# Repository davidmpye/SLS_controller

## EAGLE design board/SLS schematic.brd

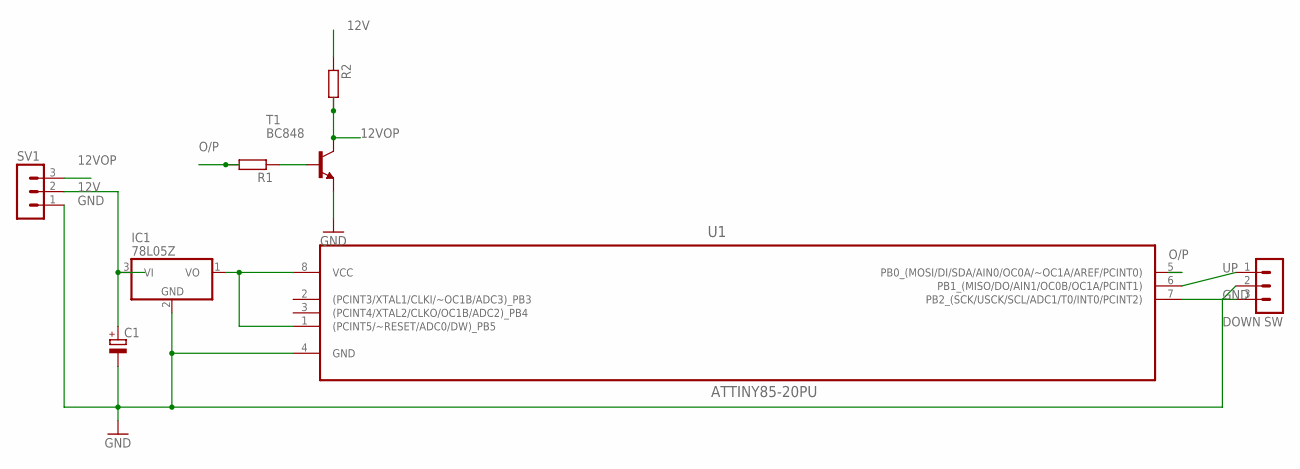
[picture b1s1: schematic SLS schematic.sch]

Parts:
C1: CPOL-EUCT3216; CT3216
IC1: 78L05Z; TO92
R1, R2: R-EU_R0805; R0805
SV1: MA03-1
SW: MA03-1
T1: BC848; SOT23
U1: ATTINY85-20PU; DIP254P762X533-8

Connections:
12V: C1.+, IC1.3 (VI), R2.1, SV1.2
12VOP: R2.2, SV1.3, T1.3 (C)
DOWN: SW.3, U1.7 (PB2_(SCK/USCK/SCL/ADC1/T0/INT0/PCINT2))
GND: C1.-, IC1.2 (GND), SV1.1, SW.2, T1.2 (E), U1.4 (GND)
unnamed: IC1.1 (VO), U1.1 ((PCINT5/~RESET/ADC0/DW)_PB5), U1.8 (VCC)
unnamed: R1.1, T1.1 (B)
O/P: R1.2, U1.5 (PB0_(MOSI/DI/SDA/AIN0/OC0A/~OC1A/AREF/P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)
UP: SW.1, U1.6 (PB1_(MISO/DO/AIN1/OC0B/OC1A/PCINT1))

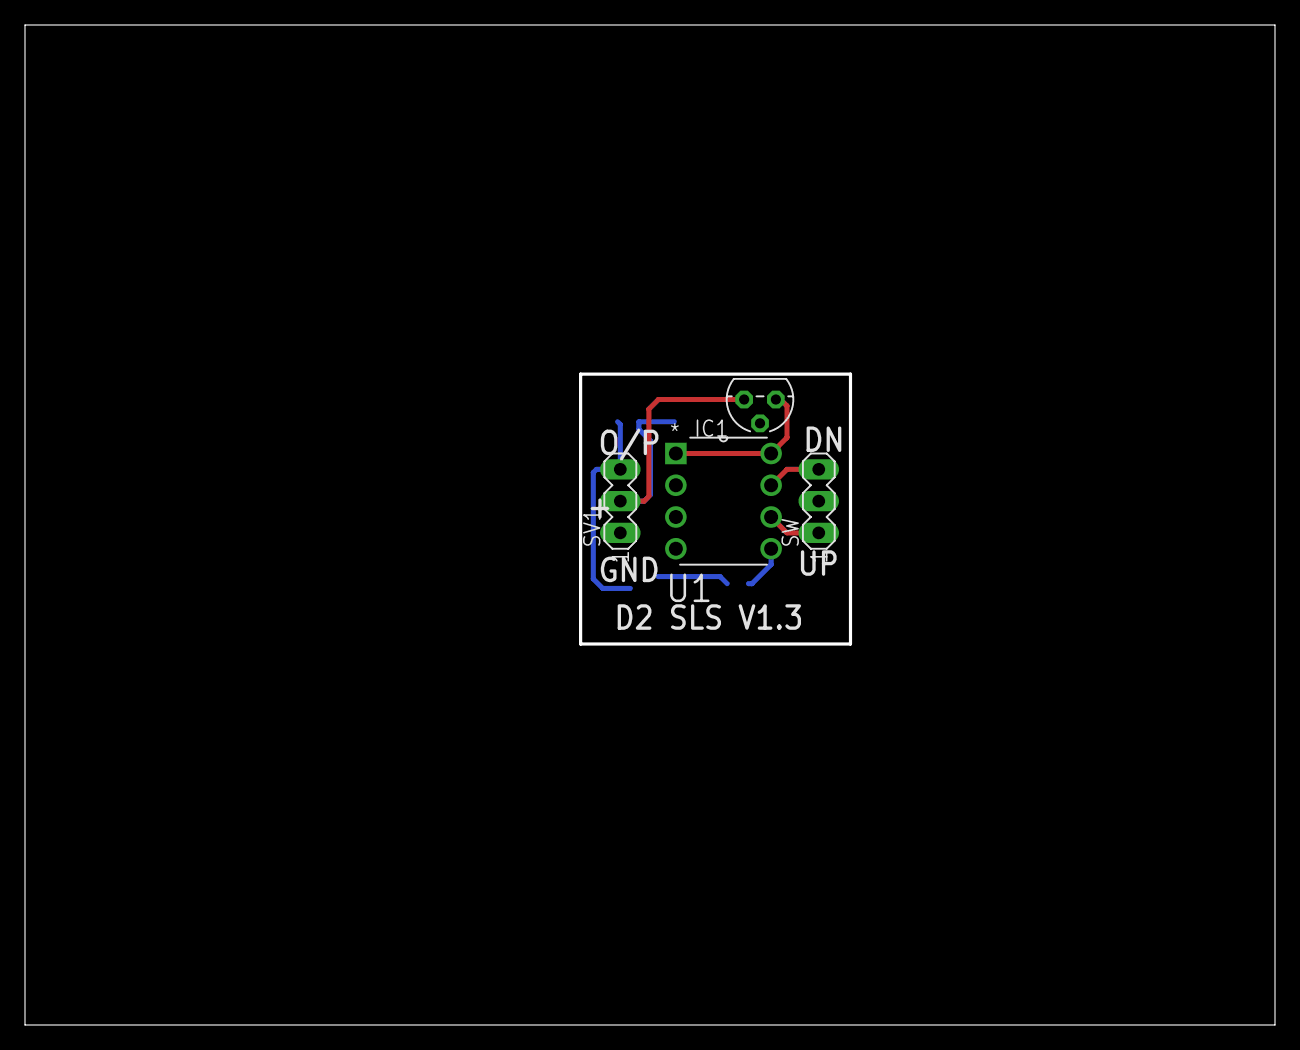
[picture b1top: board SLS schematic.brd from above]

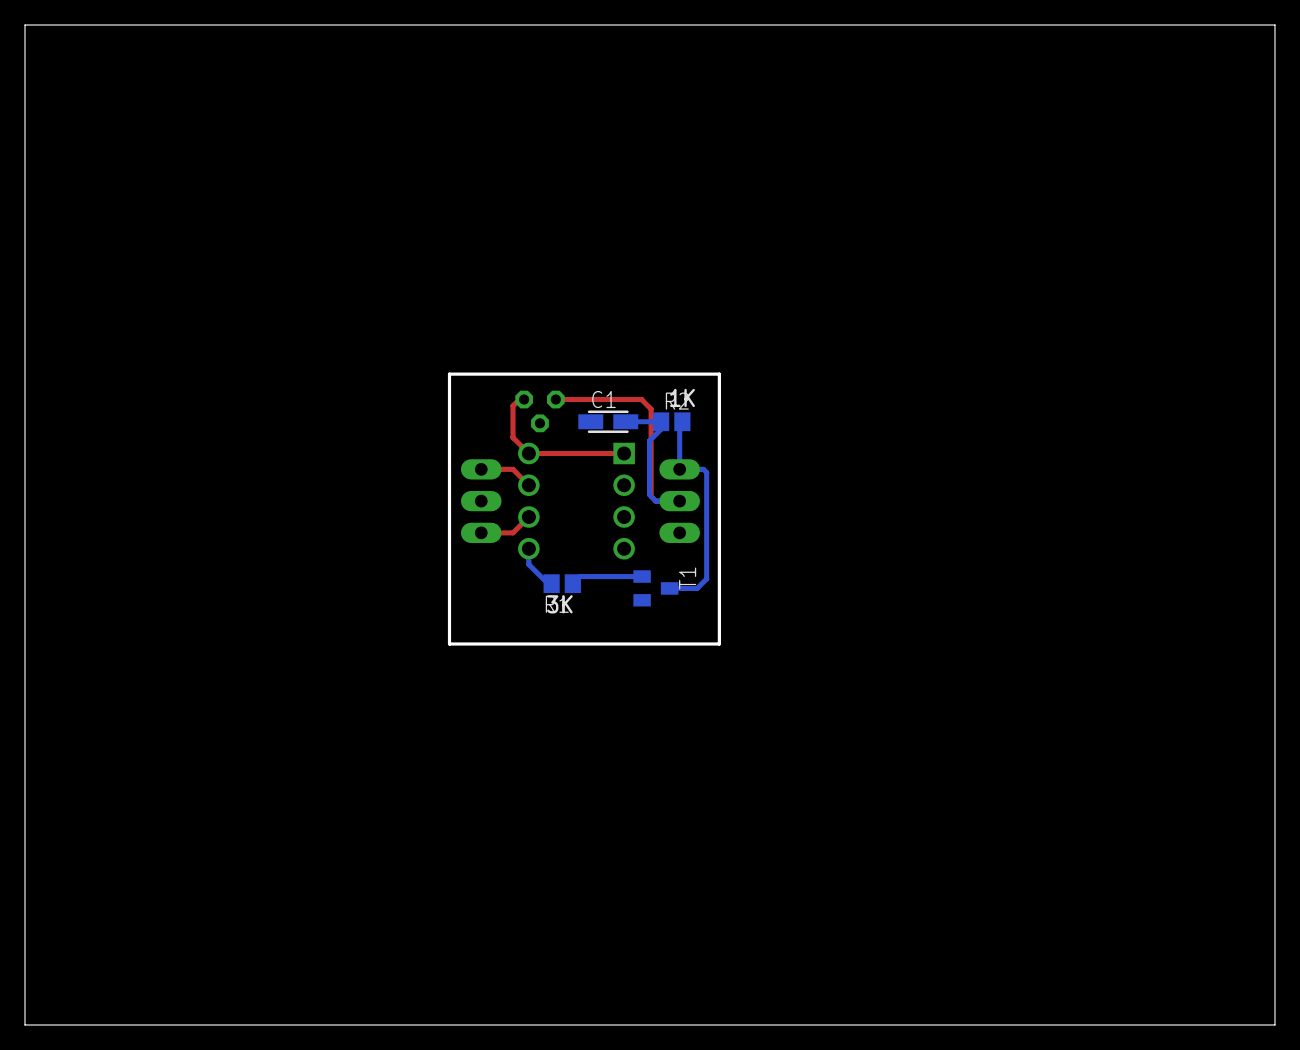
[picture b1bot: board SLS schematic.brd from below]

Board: 2 copper layers, 99.7 x 79.7 mm, 8 parts (4 on the bottom side), 8 nets.

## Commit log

2016-10-12 Initial import
2016-10-12 Board initial import
2016-10-12 Update to 1.3 v board (untested)
2017-07-29 Change project to KiCAD
2017-07-29 Add gerbers
2017-08-02 Update to make 3d view display properly
